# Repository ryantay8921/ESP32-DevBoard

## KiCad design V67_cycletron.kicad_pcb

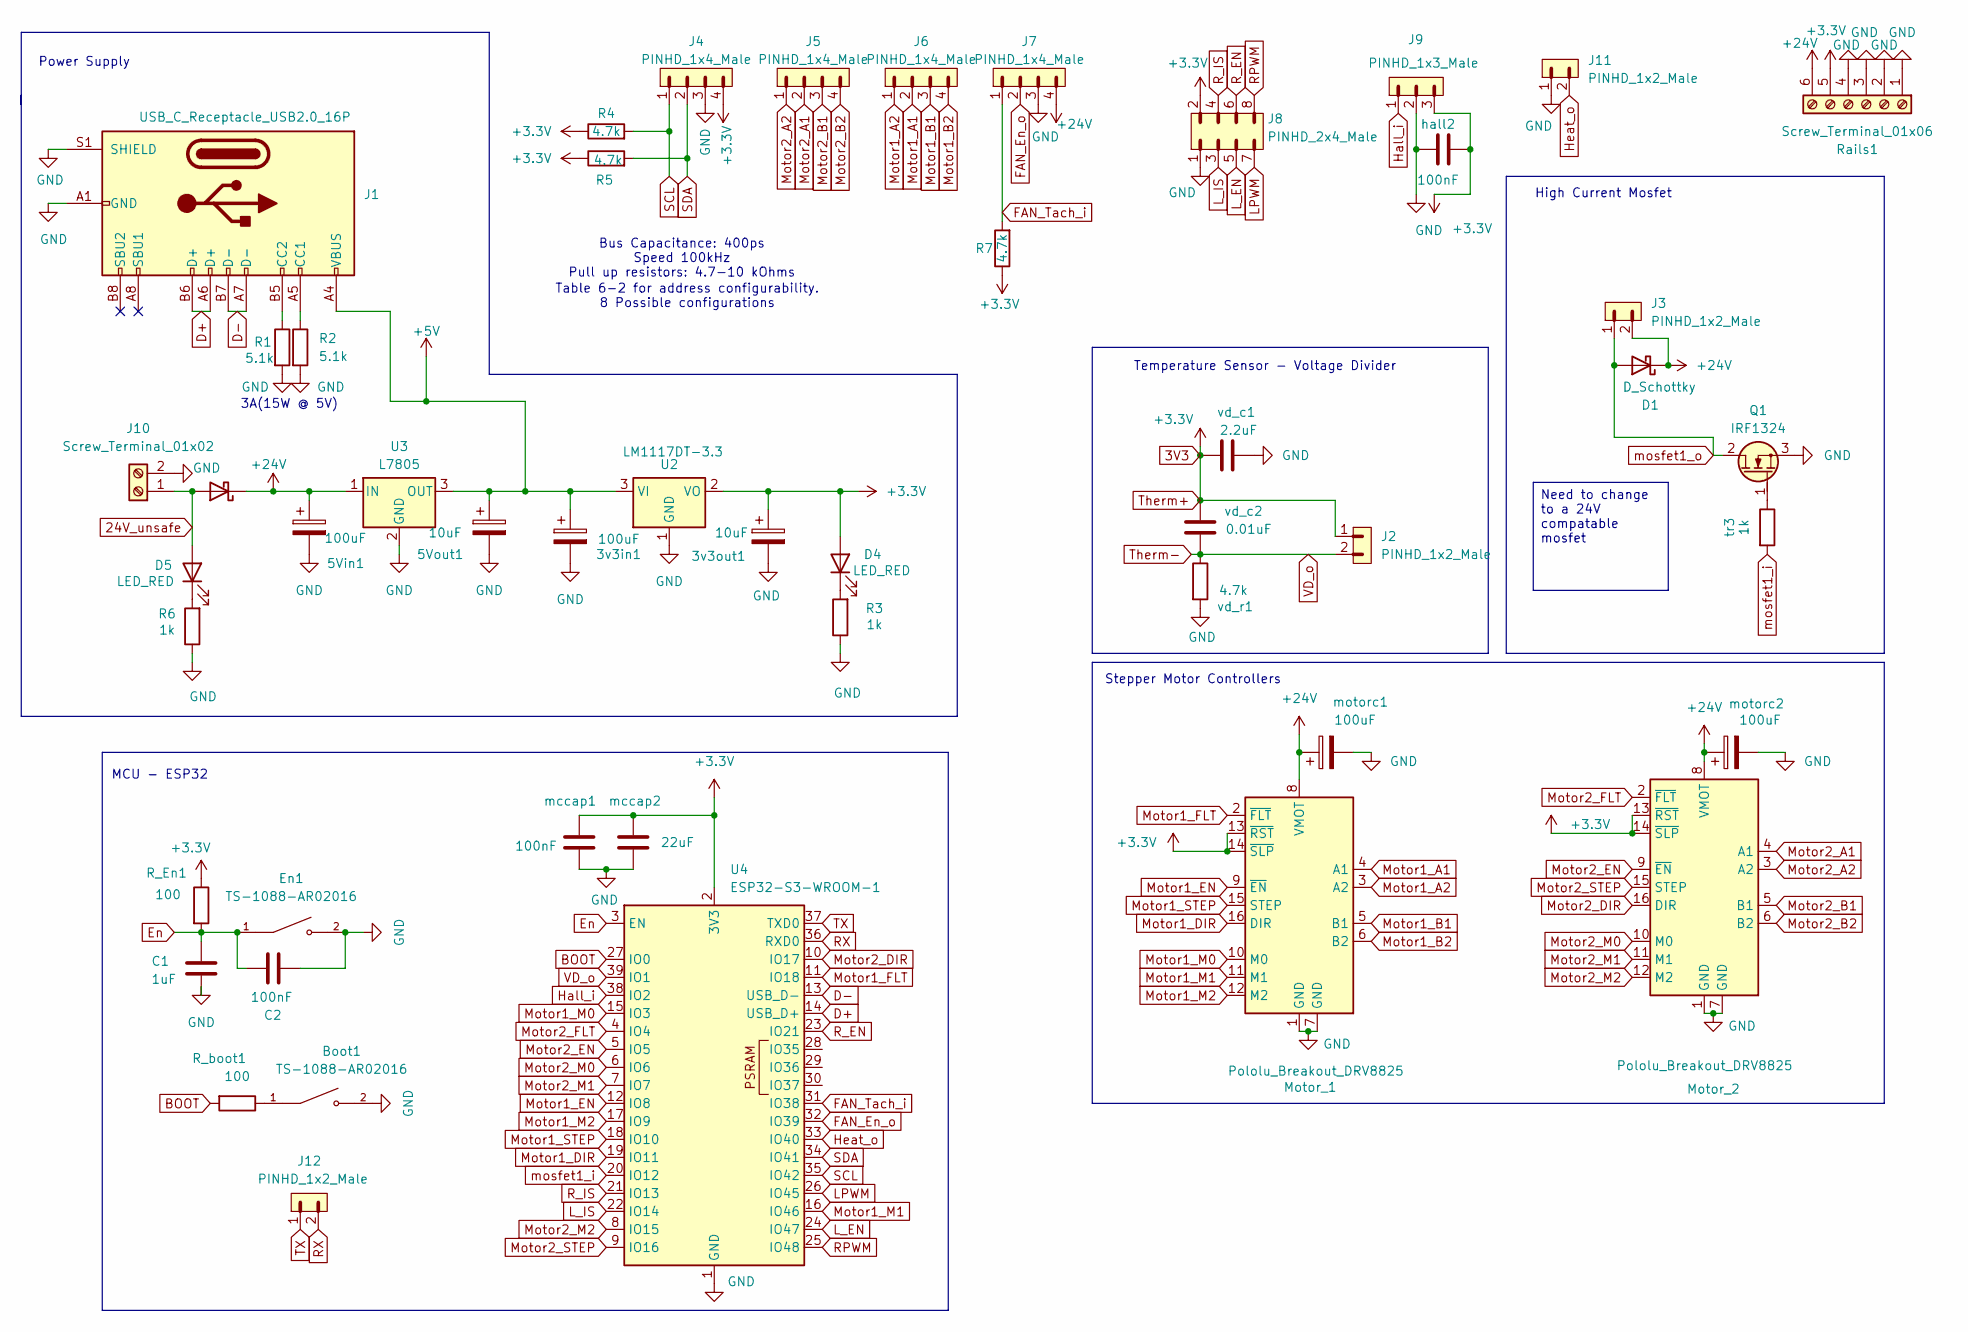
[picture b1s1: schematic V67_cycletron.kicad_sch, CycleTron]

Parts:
3v3in1, 5Vin1: 100uF; CP_Elec_6.3x5.4; LCSC C7469933
3v3out1, 5Vout1: 10uF; CP_Elec_4x5.4; LCSC C3343
Boot1: TS-1088-AR02016; SW_TS-1088-AR02016; PARTREV N/A; LCSC C720477
C1: 1uF; C_0805_2012Metric_Pad1.18x1.45mm_HandSolder; LCSC C28323
C2: 100nF; C_0805_2012Metric_Pad1.18x1.45mm_HandSolder; LCSC C28233
D1: D_Schottky; D_SMA; LCSC C22452
D4, D5: LED_RED; LED_0603_1608Metric_Pad1.05x0.95mm_HandSolder; LCSC C125099
Dpower1: D_Schottky; D_SMA; LCSC C22452
En1: TS-1088-AR02016; SW_TS-1088-AR02016; PARTREV N/A; LCSC C720477
J1: USB_C_Receptacle_USB2.0_16P; USB_C_Receptacle_HRO_TYPE-C-31-M-12; LCSC C5337088
J2, J3, J11, J12: PINHD_1x2_Male; PinHeader_1x02_P2.54mm_Vertical; LCSC C5360898
J4, J5, J6, J7: PINHD_1x4_Male; PinHeader_1x04_P2.54mm_Vertical; LCSC C5116483
J8: PINHD_2x4_Male; PinHeader_2x04_P2.54mm_Vertical; LCSC C5156679
J9: PINHD_1x3_Male; PinHeader_1x03_P2.54mm_Vertical; LCSC C5360899
J10: Screw_Terminal_01x02; TerminalBlock_MaiXu_MX126-5.0-02P_1x02_P5.00mm
Motor_1, Motor_2: Pololu_Breakout_DRV8825; Pololu_Breakout-16_15.2x20.3mm; LCSC C46061772
Q1: IRF1324; TO-220-3_Vertical_GDS; LCSC C22357145
R1, R2: 5.1k; R_0805_2012Metric_Pad1.20x1.40mm_HandSolder; LCSC C27834
R3, R6: 1k; R_0805_2012Metric_Pad1.20x1.40mm_HandSolder
R4, R5, R7: 4.7k; R_0805_2012Metric_Pad1.20x1.40mm_HandSolder
R_En1: 100; R_0805_2012Metric_Pad1.20x1.40mm_HandSolder; LCSC C17408
R_boot1: 100; R_0805_2012Metric_Pad1.20x1.40mm_HandSolder; LCSC C17408
Rails1: Screw_Terminal_01x06; TerminalBlock_MaiXu_MX126-5.0-06P_1x06_P5.00mm
U2: LM1117DT-3.3; TO-252-3_TabPin2; LCSC C969102
U3: L7805; TO255P460X1020X2008-3P; LCSC C111887
U4: ESP32-S3-WROOM-1
hall2: 100nF; C_0805_2012Metric_Pad1.18x1.45mm_HandSolder
mccap1: 100nF; C_0805_2012Metric_Pad1.18x1.45mm_HandSolder
mccap2: 22uF; C_0805_2012Metric_Pad1.18x1.45mm_HandSolder
motorc1, motorc2: 100uF; CP_Elec_6.3x5.4; LCSC C2749
tr3: 1k; R_0805_2012Metric_Pad1.20x1.40mm_HandSolder; LCSC C17513
vd_c1: 2.2uF; C_0805_2012Metric_Pad1.18x1.45mm_HandSolder; LCSC C377773
vd_c2: 0.01uF; C_0805_2012Metric_Pad1.18x1.45mm_HandSolder; LCSC C1710
vd_r1: 4.7k; R_Axial_DIN0207_L6.3mm_D2.5mm_P7.62mm_Horizontal

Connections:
3V3: 3v3out1.1, D4.2 (A), J2.1, J4.4, J8.2, J9.3, Motor_1.13 (~RST), Motor_1.14 (~SLP), Motor_2.13 (~RST), Motor_2.14 (~SLP), R4.1, R5.1, R7.1, R_En1.1, Rails1.5, U2.2 (VO), U4.2 (3V3), hall2.2, mccap1.1, mccap2.1, vd_c1.1, vd_c2.2
24V_unsafe: D5.2 (A), Dpower1.2 (A), J10.1
+5V: 3v3in1.1, 5Vout1.1, J1.A4 (VBUS), J1.A9 (VBUS), J1.B4 (VBUS), J1.B9 (VBUS), U2.3 (VI), U3.3 (OUT)
+24V: 5Vin1.1, D1.1 (K), Dpower1.1 (K), J3.2, J7.4, Motor_1.8 (VMOT), Motor_2.8 (VMOT), Rails1.6, U3.1 (IN), motorc1.1, motorc2.1
BOOT: R_boot1.2, U4.27 (IO0)
D+: J1.A6 (D+), J1.B6 (D+), U4.14 (USB_D+)
D-: J1.A7 (D-), J1.B7 (D-), U4.13 (USB_D-)
En: C1.1, C2.1, En1.1, R_En1.2, U4.3 (EN)
FAN_En_o: J7.2, U4.32 (IO39)
FAN_Tach_i: J7.1, R7.2, U4.31 (IO38)
GND: 3v3in1.2, 3v3out1.2, 5Vin1.2, 5Vout1.2, Boot1.2, C1.2, C2.2, En1.2, J1.A1 (GND), J1.A12 (GND), J1.B1 (GND), J1.B12 (GND), J1.S1 (SHIELD), J4.3, J7.3, J8.1, J9.2, J10.2, J11.1, Motor_1.1 (GND), Motor_1.7 (GND), Motor_2.1 (GND), Motor_2.7 (GND), Q1.3 (S), R1.2, R2.2, R3.1, R6.1, Rails1.1, Rails1.2, Rails1.3, Rails1.4, U2.1 (GND), U3.2 (GND), U4.1 (GND), U4.40 (GND), U4.41 (GND), hall2.1, mccap1.2, mccap2.2, motorc1.2, motorc2.2, vd_c1.2, vd_r1.2
Hall_i: J9.1, U4.38 (IO2)
Heat_o: J11.2, U4.33 (IO40)
LPWM: J8.7, U4.26 (IO45)
L_EN: J8.5, U4.24 (IO47)
L_IS: J8.3, U4.22 (IO14)
Motor1_A1: J6.2, Motor_1.4 (A1)
Motor1_A2: J6.1, Motor_1.3 (A2)
Motor1_B1: J6.3, Motor_1.5 (B1)
Motor1_B2: J6.4, Motor_1.6 (B2)
Motor1_DIR: Motor_1.16 (DIR), U4.19 (IO11)
Motor1_EN: Motor_1.9 (~EN), U4.12 (IO8)
Motor1_FLT: Motor_1.2 (~FLT), U4.11 (IO18)
Motor1_M0: Motor_1.10 (M0), U4.15 (IO3)
Motor1_M1: Motor_1.11 (M1), U4.16 (IO46)
Motor1_M2: Motor_1.12 (M2), U4.17 (IO9)
Motor1_STEP: Motor_1.15 (STEP), U4.18 (IO10)
Motor2_A1: J5.2, Motor_2.4 (A1)
Motor2_A2: J5.1, Motor_2.3 (A2)
Motor2_B1: J5.3, Motor_2.5 (B1)
Motor2_B2: J5.4, Motor_2.6 (B2)
Motor2_DIR: Motor_2.16 (DIR), U4.10 (IO17)
Motor2_EN: Motor_2.9 (~EN), U4.5 (IO5)
Motor2_FLT: Motor_2.2 (~FLT), U4.4 (IO4)
Motor2_M0: Motor_2.10 (M0), U4.6 (IO6)
Motor2_M1: Motor_2.11 (M1), U4.7 (IO7)
Motor2_M2: Motor_2.12 (M2), U4.8 (IO15)
Motor2_STEP: Motor_2.15 (STEP), U4.9 (IO16)
unnamed: Boot1.1, R_boot1.1
unnamed: D4.1 (K), R3.2
unnamed: D5.1 (K), R6.2
unnamed: J1.A5 (CC1), R2.1
unnamed: J1.B5 (CC2), R1.1
unnamed: Q1.1 (G), tr3.1
RPWM: J8.8, U4.25 (IO48)
RX: J12.2, U4.36 (RXD0)
R_EN: J8.6, U4.23 (IO21)
R_IS: J8.4, U4.21 (IO13)
SCL: J4.1, R4.2, U4.35 (IO42)
SDA: J4.2, R5.2, U4.34 (IO41)
TX: J12.1, U4.37 (TXD0)
Therm-: J2.2, U4.39 (IO1), vd_c2.1, vd_r1.1
mosfet1_i: U4.20 (IO12), tr3.2
mosfet1_o: D1.2 (A), J3.1, Q1.2 (D)

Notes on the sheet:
Table 6-2 for address configurability. 8 Possible configurations
Power Supply
3A(15W @ 5V)
High Current Mosfet
Bus Capacitance: 400ps Speed 100kHz Pull up resistors: 4.7-10 kOhms
Temperature Sensor - Voltage Divider
MCU - ESP32
Stepper Motor Controllers
Need to change to a 24V compatable mosfet

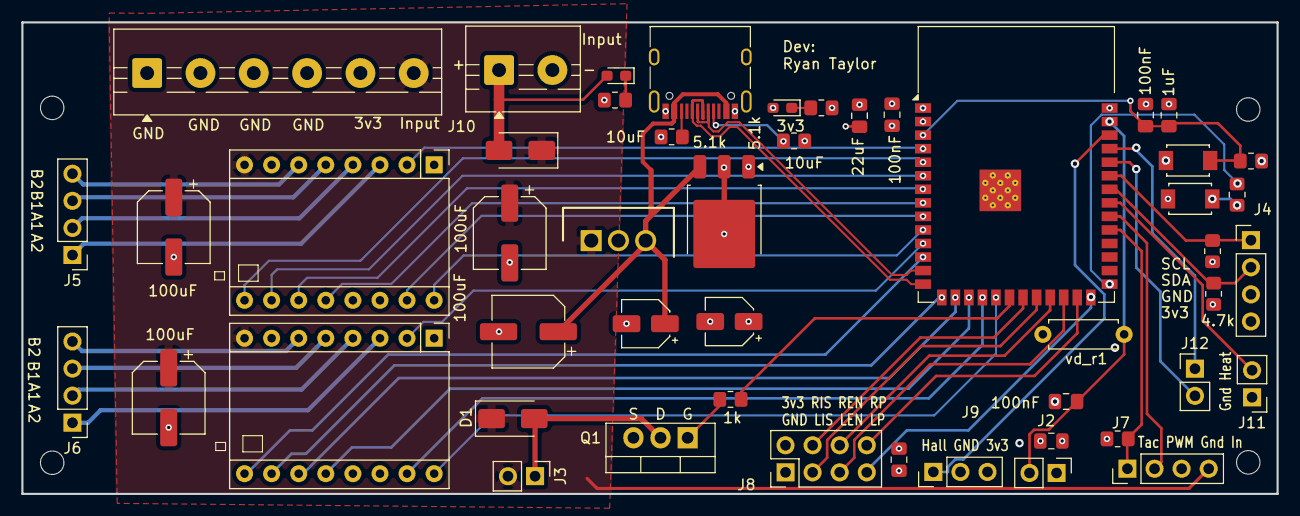
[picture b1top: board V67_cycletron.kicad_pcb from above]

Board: 4 copper layers, 117.7 x 44.2 mm, 49 parts (0 on the bottom side), 54 nets.

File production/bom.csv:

Designator,Footprint,Quantity,Value,LCSC Part #
"_4, _3, _2, ",,4,,
"3V3IN1, 5VIN1, MOTORC2",CP_Elec_6.3x5.4,3,100uF,C7469933
"3V3OUT1, 5VOUT1",CP_Elec_4x5.4,2,10uF,C3343
"BOOT1, EN1",SW_TS-1088-AR02016,2,TS-1088-AR02016,C720477
C1,0805,1,1uF,C28323
C2,0805,1,100nF,C28233
"D1, DPOWER1",D_SMA,2,D_Schottky,C22452
"D4, D5",0603,2,LED,C125099
FAN1,CONN4_B4B-PH_JST,1,PC_Fan,C566011
HALL1,CONN_B3B-PH-K-SLFSN_JST,1,Hall_Sens,C131339 
"HALL2, MCCAP1",0805,2,100nF,
HB1,JST_B6B-PH-K-S,1,B6B-PH-K-S,C495261
"HB2, INPUT1, MOS1, THERM1",JST_B2B-PH-K-S,4,B2B-PH-K-S,C5251182
I2C1,CONN4_B4B-PH_JST,1,MCP9600,C566011
J1,USB_C_Receptacle_HRO_TYPE-C-31-M-12,1,USB_C_Receptacle_USB2.0_16P,C5337088
MCCAP2,0805,1,22uF,
MOSFET4,SOT-23,1,HD2305,C466664
MOTOR1,CONN4_B4B-PH_JST,1,Motor1,C566011
MOTOR2,CONN4_B4B-PH_JST,1,Motor2,C566011
MOTORC1,CP_Elec_6.3x5.4,1,100uF,C2749
"R1, R2",0805,2,5.1k,C27834
"R3, R6",0805,2,1k,
"R4, R5, R7",0805,3,4.7k,
"R_BOOT1, R_EN1",0805,2,100,C17408
TR3,0805,1,1k,C17513
U2,TO-252-3_TabPin2,1,LM1117DT-3.3,C969102
U3,TO255P460X1020X2008-3P,1,L7805,C111887
U4,ESP32-S3-WROOM-1,1,ESP32-S3-WROOM-1,C2913199
VD_C1,0805,1,2.2uF,C377773
VD_C2,0805,1,0.01uF,C1710

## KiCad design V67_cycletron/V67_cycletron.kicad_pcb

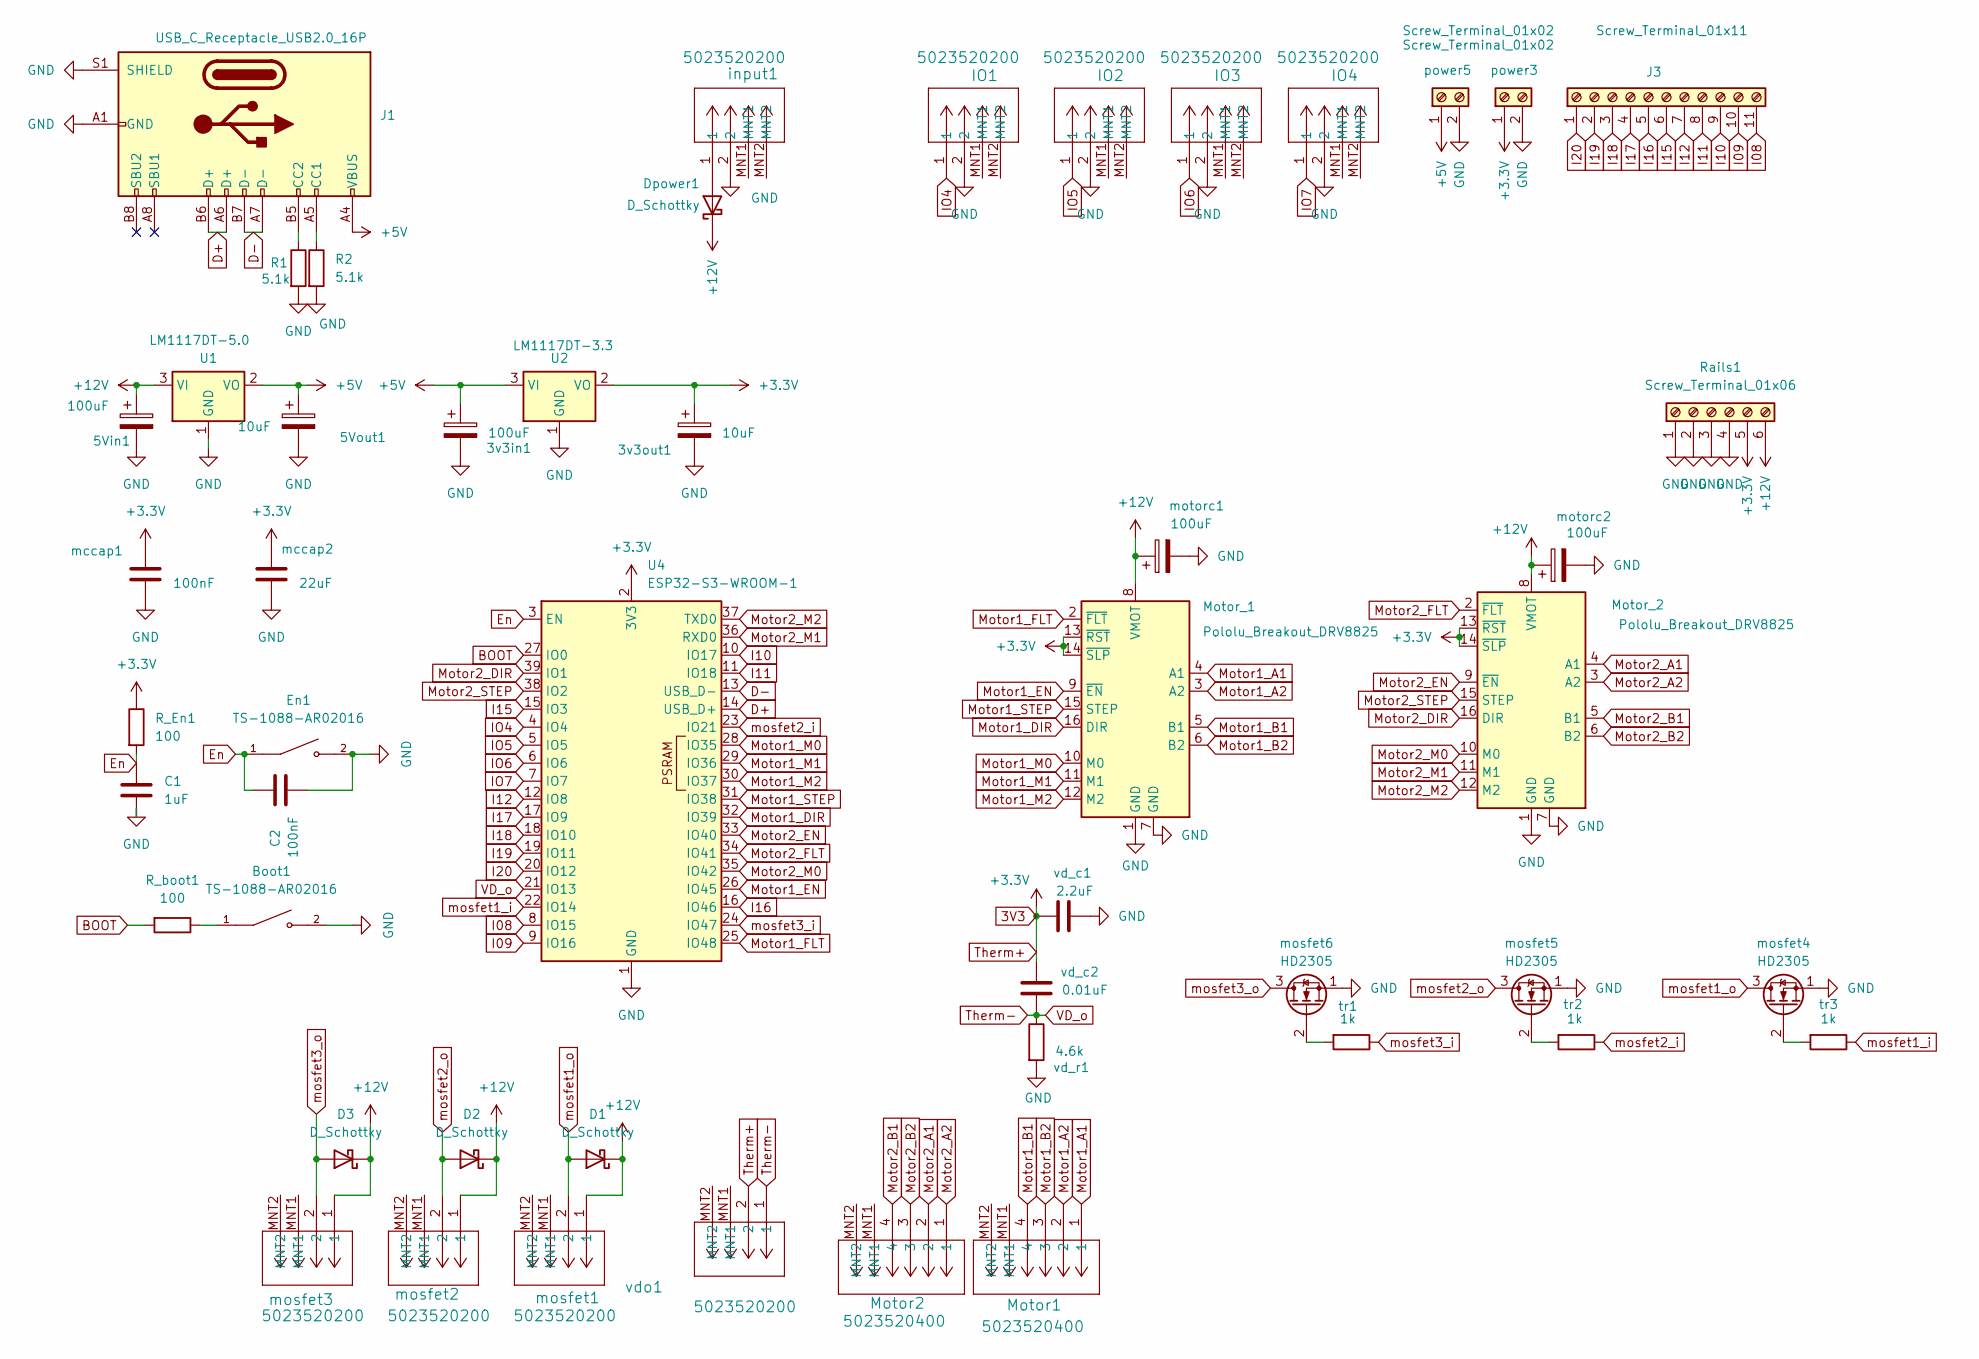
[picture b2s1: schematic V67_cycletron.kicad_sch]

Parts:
3v3in1, 5Vin1: 100uF; CP_Elec_6.3x5.4; LCSC C2749
3v3out1, 5Vout1: 10uF; CP_Elec_4x5.4; LCSC C3343
Boot1: TS-1088-AR02016; SW_TS-1088-AR02016; PARTREV N/A; LCSC C720477
C1: 1uF; C_0805_2012Metric_Pad1.18x1.45mm_HandSolder; LCSC C28323
C2: 100nF; C_0805_2012Metric_Pad1.18x1.45mm_HandSolder; LCSC C28233
D1, D2, D3: D_Schottky; D_SMA; LCSC C22452
Dpower1: D_Schottky; D_SMA; LCSC C22452
En1: TS-1088-AR02016; SW_TS-1088-AR02016; PARTREV N/A; LCSC C720477
IO1, IO2, IO3, IO4: 5023520200; CONN_SD-502352-001_02_MOL; LCSC C114107
J1: USB_C_Receptacle_USB2.0_16P; USB_C_Receptacle_HRO_TYPE-C-31-M-12; LCSC C5338271
J3: Screw_Terminal_01x11; TerminalBlock_MaiXu_MX126-5.0-11P_1x11_P5.00mm
Motor1, Motor2: 5023520400; CONN_SD-502352-001_04_MOL; LCSC C277598
Motor_1, Motor_2: Pololu_Breakout_DRV8825; Pololu_Breakout-16_15.2x20.3mm; LCSC C46061772
R1, R2: 5.1k; R_0805_2012Metric_Pad1.20x1.40mm_HandSolder; LCSC C27834
R_En1: 100; R_0805_2012Metric_Pad1.20x1.40mm_HandSolder; LCSC C17408
R_boot1: 100; R_0805_2012Metric_Pad1.20x1.40mm_HandSolder; LCSC C17408
Rails1: Screw_Terminal_01x06; TerminalBlock_MaiXu_MX126-5.0-06P_1x06_P5.00mm
U1: LM1117DT-5.0; TO-252-3_TabPin2; LCSC C354068
U2: LM1117DT-3.3; TO-252-3_TabPin2; LCSC C969102
U4: ESP32-S3-WROOM-1
input1: 5023520200; CONN_SD-502352-001_02_MOL; LCSC C114107
mccap1: 100nF; C_0805_2012Metric_Pad1.18x1.45mm_HandSolder
mccap2: 22uF; C_0805_2012Metric_Pad1.18x1.45mm_HandSolder
mosfet1, mosfet2, mosfet3: 5023520200; CONN_SD-502352-001_02_MOL; LCSC C114107
mosfet4, mosfet5, mosfet6: HD2305; SOT-23; LCSC C466664
motorc1, motorc2: 100uF; CP_Elec_6.3x5.4; LCSC C2749
power3, power5: Screw_Terminal_01x02; TerminalBlock_MaiXu_MX126-5.0-02P_1x02_P5.00mm; LCSC C5188434
tr1, tr2, tr3: 1k; R_0805_2012Metric_Pad1.20x1.40mm_HandSolder; LCSC C17513
vd_c1: 2.2uF; C_0805_2012Metric_Pad1.18x1.45mm_HandSolder; LCSC C377773
vd_c2: 0.01uF; C_0805_2012Metric_Pad1.18x1.45mm_HandSolder; LCSC C1710
vd_r1: 4.6k; R_Axial_DIN0207_L6.3mm_D2.5mm_P7.62mm_Horizontal
vdo1: 5023520200; CONN_SD-502352-001_02_MOL; LCSC C114107

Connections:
3V3: 3v3out1.1, Motor_1.13 (~RST), Motor_1.14 (~SLP), Motor_2.13 (~RST), Motor_2.14 (~SLP), R_En1.1, Rails1.5, U2.2 (VO), U4.2 (3V3), mccap1.1, mccap2.1, power3.1, vd_c1.1, vd_c2.2, vdo1.2; also elsewhere on the board
+5V: 3v3in1.1, 5Vout1.1, J1.A4 (VBUS), J1.A9 (VBUS), J1.B4 (VBUS), J1.B9 (VBUS), U1.2 (VO), U2.3 (VI), power5.1
+12V: 5Vin1.1, D1.1 (K), D2.1 (K), D3.1 (K), Dpower1.1 (K), Motor_1.8 (VMOT), Motor_2.8 (VMOT), Rails1.6, U1.3 (VI), mosfet1.1, mosfet2.1, mosfet3.1, motorc1.1, motorc2.1
BOOT: R_boot1.2, U4.27 (IO0); also elsewhere on the board
D+: J1.A6 (D+), J1.B6 (D+), U4.14 (USB_D+); also elsewhere on the board
D-: J1.A7 (D-), J1.B7 (D-), U4.13 (USB_D-); also elsewhere on the board
En: C1.1, C2.1, En1.1, R_En1.2, U4.3 (EN); also elsewhere on the board
GND: 3v3in1.2, 3v3out1.2, 5Vin1.2, 5Vout1.2, Boot1.2, C1.2, C2.2, En1.2, IO1.2, IO2.2, IO3.2, IO4.2, J1.A1 (GND), J1.A12 (GND), J1.B1 (GND), J1.B12 (GND), J1.S1 (SHIELD), Motor_1.1 (GND), Motor_1.7 (GND), Motor_2.1 (GND), Motor_2.7 (GND), R1.2, R2.2, Rails1.1, Rails1.2, Rails1.3, Rails1.4, U1.1 (GND), U2.1 (GND), U4.1 (GND), U4.40 (GND), U4.41 (GND), input1.2, mccap1.2, mccap2.2, mosfet4.1 (S), mosfet5.1 (S), mosfet6.1 (S), motorc1.2, motorc2.2, power3.2, power5.2, vd_c1.2, vd_r1.2; also elsewhere on the board
I08: J3.11, U4.8 (IO15); also elsewhere on the board
I09: J3.10, U4.9 (IO16); also elsewhere on the board
I10: J3.9, U4.10 (IO17); also elsewhere on the board
I11: J3.8, U4.11 (IO18); also elsewhere on the board
I12: J3.7, U4.12 (IO8); also elsewhere on the board
I15: J3.6, U4.15 (IO3); also elsewhere on the board
I16: J3.5, U4.16 (IO46); also elsewhere on the board
I17: J3.4, U4.17 (IO9); also elsewhere on the board
I18: J3.3, U4.18 (IO10); also elsewhere on the board
I19: J3.2, U4.19 (IO11); also elsewhere on the board
I20: J3.1, U4.20 (IO12); also elsewhere on the board
IO4: IO1.1, U4.4 (IO4); also elsewhere on the board
IO5: IO2.1, U4.5 (IO5); also elsewhere on the board
IO6: IO3.1, U4.6 (IO6); also elsewhere on the board
IO7: IO4.1, U4.7 (IO7); also elsewhere on the board
Motor1_A1: Motor1.1, Motor_1.4 (A1)
Motor1_A2: Motor1.2, Motor_1.3 (A2)
Motor1_B1: Motor1.4, Motor_1.5 (B1)
Motor1_B2: Motor1.3, Motor_1.6 (B2)
Motor1_DIR: Motor_1.16 (DIR), U4.32 (IO39); also elsewhere on the board
Motor1_EN: Motor_1.9 (~EN), U4.26 (IO45); also elsewhere on the board
Motor1_FLT: Motor_1.2 (~FLT), U4.25 (IO48); also elsewhere on the board
Motor1_M0: Motor_1.10 (M0), U4.28 (IO35); also elsewhere on the board
Motor1_M1: Motor_1.11 (M1), U4.29 (IO36); also elsewhere on the board
Motor1_M2: Motor_1.12 (M2), U4.30 (IO37); also elsewhere on the board
Motor1_STEP: Motor_1.15 (STEP), U4.31 (IO38); also elsewhere on the board
Motor2_A1: Motor2.2, Motor_2.4 (A1)
Motor2_A2: Motor2.1, Motor_2.3 (A2)
Motor2_B1: Motor2.4, Motor_2.5 (B1)
Motor2_B2: Motor2.3, Motor_2.6 (B2)
Motor2_DIR: Motor_2.16 (DIR), U4.39 (IO1); also elsewhere on the board
Motor2_EN: Motor_2.9 (~EN), U4.33 (IO40); also elsewhere on the board
Motor2_FLT: Motor_2.2 (~FLT), U4.34 (IO41); also elsewhere on the board
Motor2_M0: Motor_2.10 (M0), U4.35 (IO42); also elsewhere on the board
Motor2_M1: Motor_2.11 (M1), U4.36 (RXD0); also elsewhere on the board
Motor2_M2: Motor_2.12 (M2), U4.37 (TXD0); also elsewhere on the board
Motor2_STEP: Motor_2.15 (STEP), U4.38 (IO2); also elsewhere on the board
unnamed: Boot1.1, R_boot1.1
unnamed: Dpower1.2 (A), input1.1
unnamed: J1.A5 (CC1), R2.1
unnamed: J1.B5 (CC2), R1.1
unnamed: mosfet4.2 (G), tr3.2
unnamed: mosfet5.2 (G), tr2.2
unnamed: mosfet6.2 (G), tr1.2
Therm-: U4.21 (IO13), vd_c2.1, vd_r1.1, vdo1.1; also elsewhere on the board
mosfet1_i: U4.22 (IO14), tr3.1; also elsewhere on the board
mosfet1_o: D1.2 (A), mosfet1.2, mosfet4.3 (D)
mosfet2_i: U4.23 (IO21), tr2.1; also elsewhere on the board
mosfet2_o: D2.2 (A), mosfet2.2, mosfet5.3 (D)
mosfet3_i: U4.24 (IO47), tr1.1; also elsewhere on the board
mosfet3_o: D3.2 (A), mosfet3.2, mosfet6.3 (D)

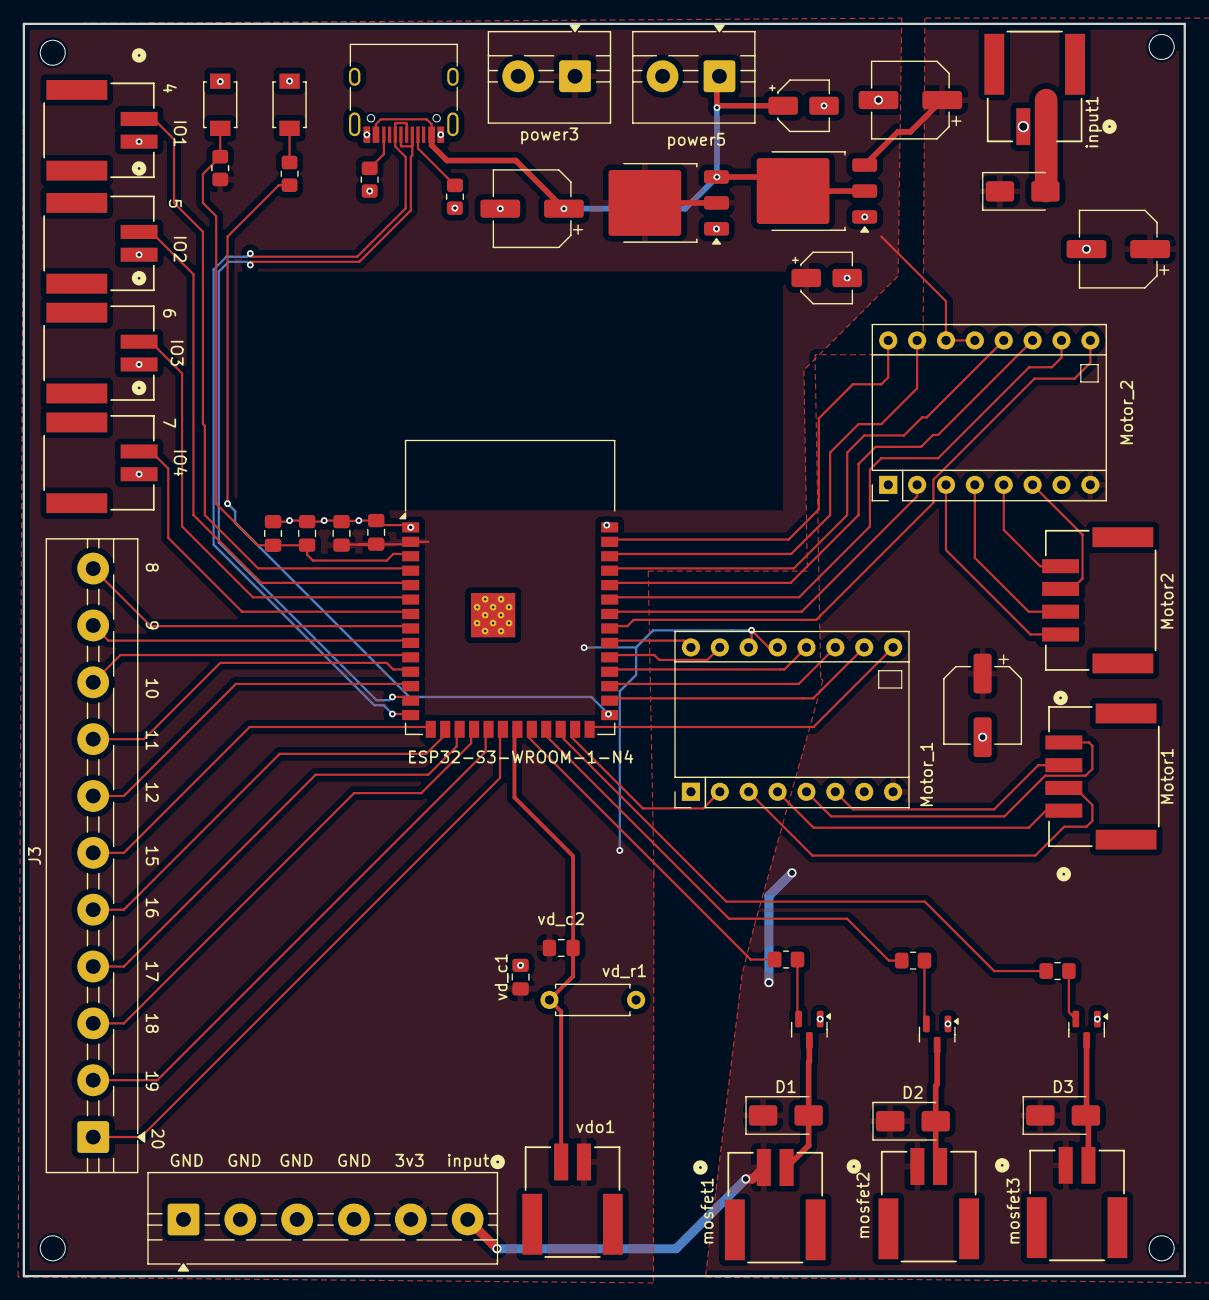
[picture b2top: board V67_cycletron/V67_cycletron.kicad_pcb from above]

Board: 2 copper layers, 102.1 x 110.1 mm, 50 parts (0 on the bottom side), 59 nets.

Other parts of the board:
ESP32-S3-WROOM-1-N4: ESP32-S3-WROOM-1

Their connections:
3V3: ESP32-S3-WROOM-1-N4.2 (3V3); also elsewhere on the board
BOOT: ESP32-S3-WROOM-1-N4.27 (IO0); also elsewhere on the board
D+: ESP32-S3-WROOM-1-N4.14 (USB_D+); also elsewhere on the board
D-: ESP32-S3-WROOM-1-N4.13 (USB_D-); also elsewhere on the board
En: ESP32-S3-WROOM-1-N4.3 (EN); also elsewhere on the board
GND: ESP32-S3-WROOM-1-N4.1 (GND), ESP32-S3-WROOM-1-N4.40 (GND), ESP32-S3-WROOM-1-N4.41 (GND); also elsewhere on the board
I08: ESP32-S3-WROOM-1-N4.8 (IO15); also elsewhere on the board
I09: ESP32-S3-WROOM-1-N4.9 (IO16); also elsewhere on the board
I10: ESP32-S3-WROOM-1-N4.10 (IO17); also elsewhere on the board
I11: ESP32-S3-WROOM-1-N4.11 (IO18); also elsewhere on the board
I12: ESP32-S3-WROOM-1-N4.12 (IO8); also elsewhere on the board
I15: ESP32-S3-WROOM-1-N4.15 (IO3); also elsewhere on the board
I16: ESP32-S3-WROOM-1-N4.16 (IO46); also elsewhere on the board
I17: ESP32-S3-WROOM-1-N4.17 (IO9); also elsewhere on the board
I18: ESP32-S3-WROOM-1-N4.18 (IO10); also elsewhere on the board
I19: ESP32-S3-WROOM-1-N4.19 (IO11); also elsewhere on the board
I20: ESP32-S3-WROOM-1-N4.20 (IO12); also elsewhere on the board
IO4: ESP32-S3-WROOM-1-N4.4 (IO4); also elsewhere on the board
IO5: ESP32-S3-WROOM-1-N4.5 (IO5); also elsewhere on the board
IO6: ESP32-S3-WROOM-1-N4.6 (IO6); also elsewhere on the board
IO7: ESP32-S3-WROOM-1-N4.7 (IO7); also elsewhere on the board
Motor1_DIR: ESP32-S3-WROOM-1-N4.32 (IO39); also elsewhere on the board
Motor1_EN: ESP32-S3-WROOM-1-N4.26 (IO45); also elsewhere on the board
Motor1_FLT: ESP32-S3-WROOM-1-N4.25 (IO48); also elsewhere on the board
Motor1_M0: ESP32-S3-WROOM-1-N4.28 (IO35); also elsewhere on the board
Motor1_M1: ESP32-S3-WROOM-1-N4.29 (IO36); also elsewhere on the board
Motor1_M2: ESP32-S3-WROOM-1-N4.30 (IO37); also elsewhere on the board
Motor1_STEP: ESP32-S3-WROOM-1-N4.31 (IO38); also elsewhere on the board
Motor2_DIR: ESP32-S3-WROOM-1-N4.39 (IO1); also elsewhere on the board
Motor2_EN: ESP32-S3-WROOM-1-N4.33 (IO40); also elsewhere on the board
Motor2_FLT: ESP32-S3-WROOM-1-N4.34 (IO41); also elsewhere on the board
Motor2_M0: ESP32-S3-WROOM-1-N4.35 (IO42); also elsewhere on the board
Motor2_M1: ESP32-S3-WROOM-1-N4.36 (RXD0); also elsewhere on the board
Motor2_M2: ESP32-S3-WROOM-1-N4.37 (TXD0); also elsewhere on the board
Motor2_STEP: ESP32-S3-WROOM-1-N4.38 (IO2); also elsewhere on the board
Therm-: ESP32-S3-WROOM-1-N4.21 (IO13); also elsewhere on the board
mosfet1_i: ESP32-S3-WROOM-1-N4.22 (IO14); also elsewhere on the board
mosfet2_i: ESP32-S3-WROOM-1-N4.23 (IO21); also elsewhere on the board
mosfet3_i: ESP32-S3-WROOM-1-N4.24 (IO47); also elsewhere on the board

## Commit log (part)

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2026-04-06 first commit of board
2026-04-06 test commit, added schotsky diode
2026-04-07 got all parts to sync to jlcpcb
2026-04-07 moved IO
2026-04-07 fixed some issues with vias and motor connector placement
2026-04-10 changed some stuff
2026-04-10 changed some stuff 2
2026-04-10 changed some stuff 3
2026-04-10 changed mosfets added more terminals
2026-04-12 fixed drc, added silscreen notes, made certain vias bigger
2026-04-14 purchased boards
2026-04-23 Push verified PCB
2026-04-27 edited silkscreen
2026-05-03 created pin mapping xlsx and test script
2026-06-24 updates from laptop airport
2026-06-26 board layout redesign
